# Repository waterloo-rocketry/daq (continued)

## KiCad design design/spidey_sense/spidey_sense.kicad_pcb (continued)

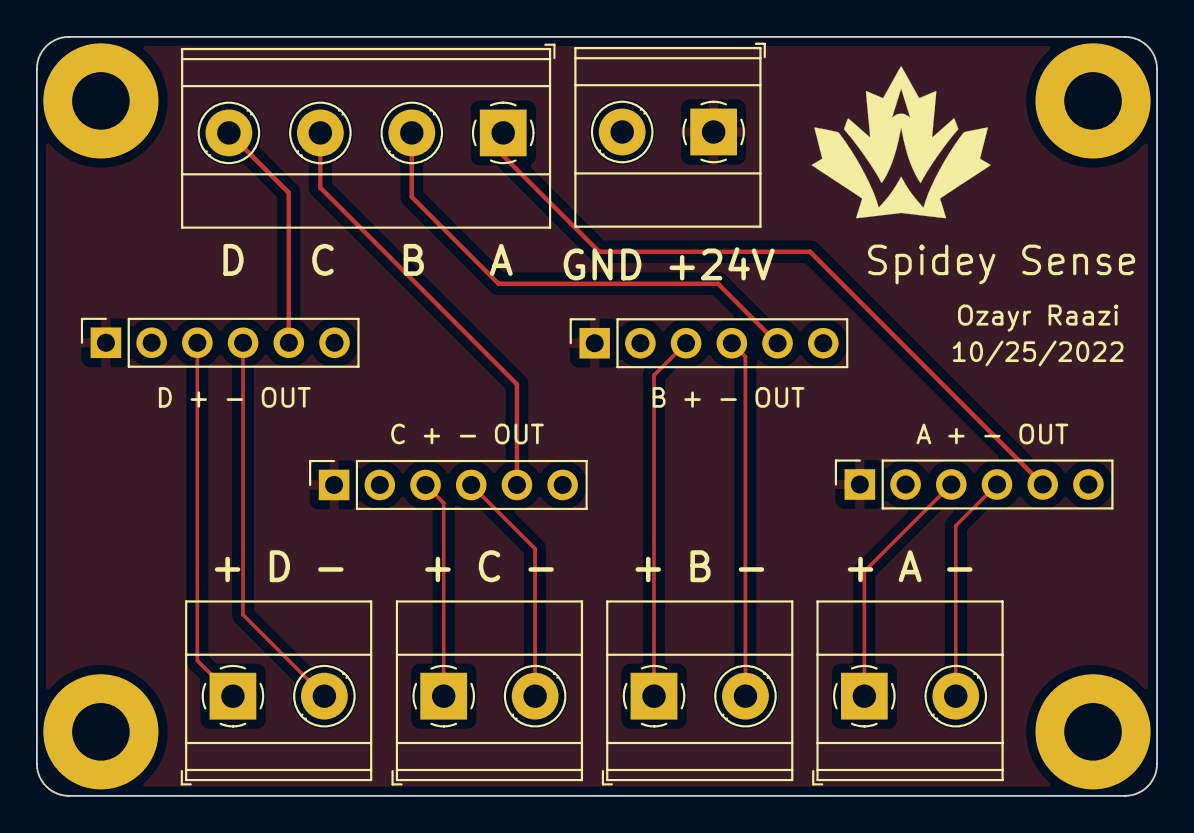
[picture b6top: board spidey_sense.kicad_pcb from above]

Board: 2 copper layers, 62.2 x 42.2 mm, 11 parts (0 on the bottom side), 14 nets.

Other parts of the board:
REF: MountingHole_3.2mm_M3_Pad

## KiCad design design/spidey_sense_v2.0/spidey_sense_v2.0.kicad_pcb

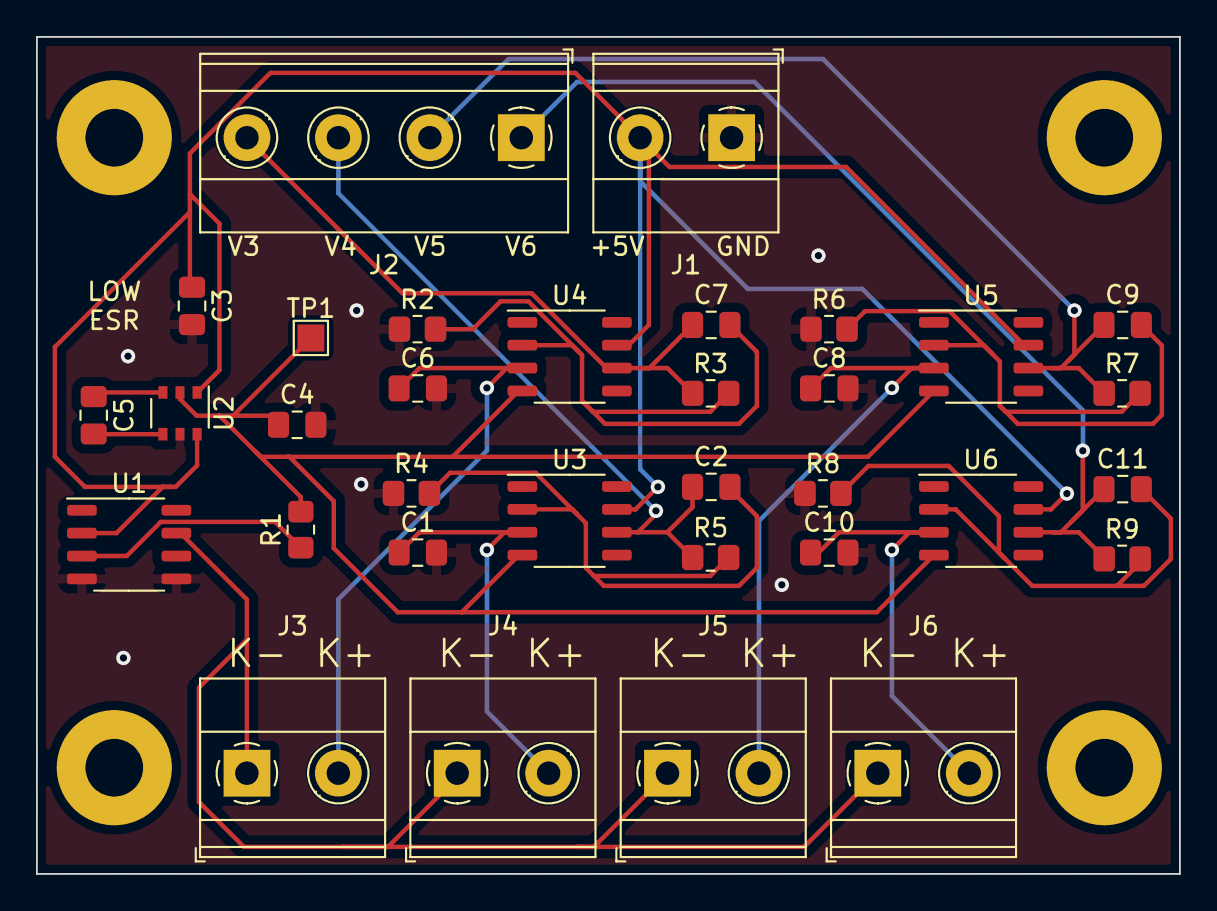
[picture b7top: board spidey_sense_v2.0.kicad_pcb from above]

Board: 2 copper layers, 63.5 x 46.5 mm, 33 parts (0 on the bottom side), 19 nets.

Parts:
C1, C2, C6, C7, C8, C9, C10, C11: 0.1uF; C_0805_2012Metric_Pad1.18x1.45mm_HandSolder
C3, C4: 10uF; C_0805_2012Metric_Pad1.18x1.45mm_HandSolder
C5: 1uF; C_0805_2012Metric_Pad1.18x1.45mm_HandSolder
J1: Input_Screw_Terminal; TerminalBlock_Phoenix_MKDS-1,5-2-5.08_1x02_P5.08mm_Horizont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
J2: Output_Screw_Terminal; TerminalBlock_Phoenix_MKDS-1,5-4-5.08_1x04_P5.08mm_Horizont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
J3, J4, J5, J6: Thermocouple_Terminal; TerminalBlock_Phoenix_MKDS-1,5-2-5.08_1x02_P5.08mm_Horizont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
R1: 150kΩ; R_0805_2012Metric_Pad1.20x1.40mm_HandSolder
R2, R4, R6, R8: 1kΩ; R_0805_2012Metric_Pad1.20x1.40mm_HandSolder
R3, R5, R7, R9: 17.3kΩ; R_0805_2012Metric_Pad1.20x1.40mm_HandSolder
TP1: TestPoint; TestPoint_Pad_1.5x1.5mm
U1: LT1025; SOP-8_3.9x4.9mm_P1.27mm
U2: LTC1983-5; TSOP-6_1.65x3.05mm_P0.95mm
U3, U4, U5, U6: LT1001; SOP-8_3.9x4.9mm_P1.27mm

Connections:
+5V: C3.1, J1.2, U1.2 (Vin), U2.1 (Vcc), U2.6 (SHDN), U3.7 (V+), U4.7 (V+), U5.7 (V+), U6.7 (V+)
-5V: C4.1, R1.2, TP1.1, U2.2 (Vout), U3.4 (V-), U4.4 (V-), U5.4 (V-), U6.4 (V-)
/Amplifier1/K+: C6.1, J3.2, U4.3 (+IN)
/Amplifier1/Vout: C7.1, J2.4, R3.1, U4.6 (OUT)
/Amplifier2/K+: C1.1, J4.2, U3.3 (+IN)
/Amplifier2/Vout: C2.1, J2.3, R5.1, U3.6 (OUT)
/Amplifier3/K+: C8.1, J5.2, U5.3 (+IN)
/Amplifier3/Vout: C9.1, J2.2, R7.1, U5.6 (OUT)
/Amplifier4/K+: C10.1, J6.2, U6.3 (+IN)
/Amplifier4/Vout: C11.1, J2.1, R9.1, U6.6 (OUT)
/K-: J3.1, J4.1, J5.1, J6.1, U1.7 (K/T)
GND: C1.2, C3.2, C4.2, C6.2, C8.2, C10.2, J1.1, R2.1, R4.1, R6.1, R8.1, U1.4 (GND), U1.5 (R-), U2.5 (GND)
unnamed: C2.2, R4.2, R5.2, U3.2 (-IN)
unnamed: C5.1, U2.3 (C+)
unnamed: C5.2, U2.4 (C-)
unnamed: C7.2, R2.2, R3.2, U4.2 (-IN)
unnamed: C9.2, R6.2, R7.2, U5.2 (-IN)
unnamed: C11.2, R8.2, R9.2, U6.2 (-IN)
unnamed: R1.1, U1.3 (V0)

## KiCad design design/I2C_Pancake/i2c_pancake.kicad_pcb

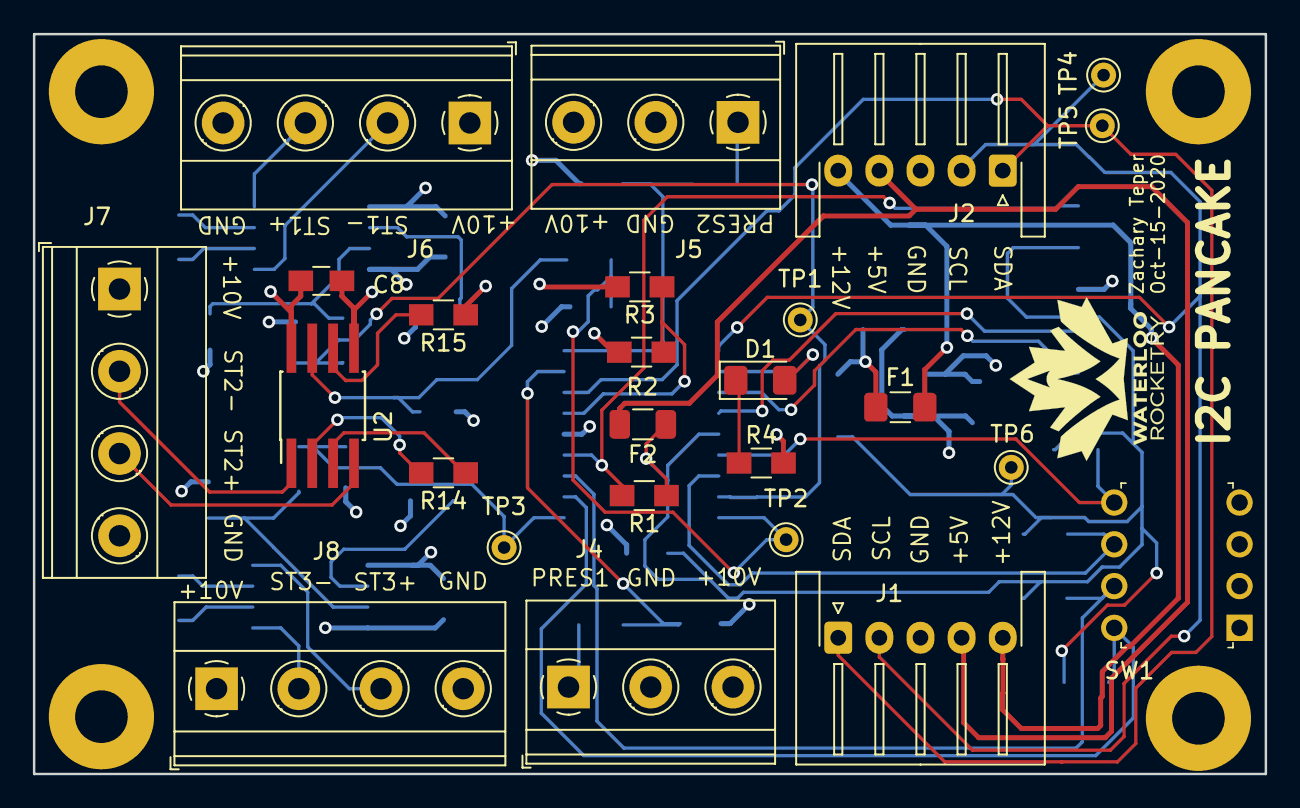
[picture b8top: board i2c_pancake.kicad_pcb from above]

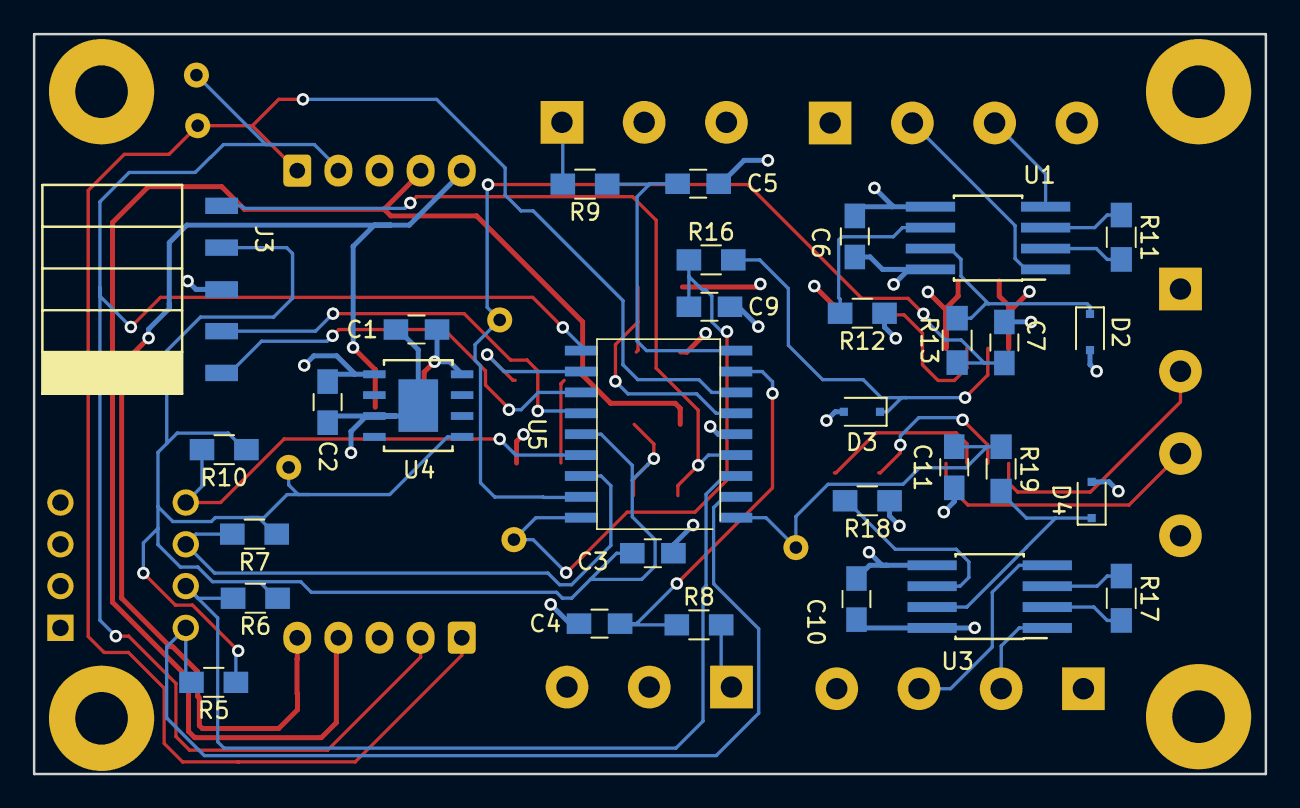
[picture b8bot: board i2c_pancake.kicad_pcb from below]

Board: 4 copper layers, 74.9 x 45.0 mm, 56 parts (31 on the bottom side), 43 nets.

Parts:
C1, C2, C4, C5, C7, C9, C11: 1 uF; C_0805_HandSoldering
C3, C6, C8, C10: 0.1uF; C_0805_HandSoldering
D1: LED; LED_1206_3216Metric_Pad1.42x1.75mm_HandSolder
D2, D3, D4: DDZ4V7ASF-7; D_SOD-323F
F1: Fuse; Fuse_1206_3216Metric_Pad1.42x1.75mm_HandSolder
F2: Fuse; Fuse_1206_3216Metric
J1, J2: Conn_01x05_Male; JST_XH_S5B-XH-A-1_1x05_P2.50mm_Horizontal
J3: Conn_01x05_Female; PinHeader_5x2.54_SMD_90deg_952-3198-1-ND
J4, J5: Conn_01x03; TerminalBlock_Phoenix_MKDS-1,5-3_1x03_P5.00mm_Horizontal
J6, J7, J8: Conn_01x04; TerminalBlock_Phoenix_MKDS-1,5-4_1x04_P5.00mm_Horizontal
R1, R2, R5, R6, R7, R10: 10K; R_0805_HandSoldering
R3: 5K; R_0805_HandSoldering
R4: 330; R_0805_HandSoldering
R8, R9, R13, R16, R19: 150; R_0805_HandSoldering
R11, R14, R17: R; R_0805_HandSoldering
R12, R15, R18: 0; R_0805_HandSoldering
SW1: SW_DIP_x04; DIP_SWITCH_4X2
TP1, TP2, TP3, TP4, TP5, TP6: TestPoint
U1, U2, U3: INA826; SOIC-8_3.9x4.9mm_Pitch1.27mm_HandSoldering
U4: BDJ0FC0WEFJ-E2
U5: PIC16F1826-ISO

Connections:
+5V: F2.2, J1.4, J2.4
+10V: C2.1, C6.2, C8.2, C10.2, J4.3, J5.3, J6.1, J7.1, J8.1, R2.1, U1.8, U2.8, U3.8, U4.1
+12V: F1.2, J1.5, J2.5
/DIP_1: R5.2, SW1.8, U5.2
/DIP_2: R6.2, SW1.7, U5.3
/DIP_3: R7.2, SW1.6, U5.16
/DIP_4: R10.2, SW1.5, U5.15
/ICSPCLK: J3.1, U5.12
/ICSPDAT: J3.2, U5.13
/P1_IN: J4.1, R8.2
/P2_IN: J5.1, R9.2
/PRESSURE_1: C4.1, R8.1, U5.8
/PRESSURE_2: C5.1, R9.1, U5.9
/SCL: J1.2, J2.2, TP4.1, U5.10
/SDA: J1.1, J2.1, TP5.1, U5.7
/STRAIN_OUT_1: C7.1, R13.1, TP1.1, U5.17
/STRAIN_OUT_2: C9.1, R16.1, TP2.1, U5.18
/STRAIN_OUT_3: C11.1, R19.1, TP3.1, U5.1
/~MCLR: J3.5, R1.2, U5.4
GND: C1.2, C2.2, C3.1, C4.2, C5.2, C6.1, C7.2, C8.1, C9.2, C10.1, C11.2, D2.2, D3.2, D4.2, J1.3, J2.3, J3.3, J4.2, J5.2, J6.4, J7.4, J8.4, R3.2, R4.2, R12.1, R15.1, R18.1, SW1.1, SW1.2, SW1.3, SW1.4, U1.5, U2.5, U3.5, U4.3, U4.EPAD, U5.5
unnamed: C1.1, F1.1, U4.8
unnamed: D1.1, R4.1
unnamed: D1.2, U5.11
unnamed: D2.1, R13.2, U1.7
unnamed: D3.1, R16.2, U2.7
unnamed: D4.1, R19.2, U3.7
unnamed: J6.2, U1.1
unnamed: J6.3, U1.4
unnamed: J7.2, U2.1
unnamed: J7.3, U2.4
unnamed: J8.2, U3.1
unnamed: J8.3, U3.4
unnamed: R2.2, R3.1, U5.6
unnamed: R11.1, U1.3
unnamed: R11.2, U1.2
unnamed: R12.2, U1.6
unnamed: R14.1, U2.3
unnamed: R14.2, U2.2
unnamed: R15.2, U2.6
unnamed: R17.1, U3.3
unnamed: R17.2, U3.2
unnamed: R18.2, U3.6
VDD: C3.2, F2.1, J3.4, R1.1, R5.1, R6.1, R7.1, R10.1, TP6.1, U4.5, U5.14

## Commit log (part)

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2017-12-23 Initial commit
    Add old schematics, datasheets, and strain gauge
    circuit preliminary design.
2017-12-25 Remove unused datasheets
2017-12-25 Add old labview and arduino code, NI manual
2017-12-27 Add git attributes
2018-01-02 Fix voltage monitoring, add gitignore
2018-01-04 Preliminary board layout (no tracks)
2018-01-04 Revised board layout
    - move screw terminal locations
    - power op amps from 10V line
    - misc connector numbering switches
2018-01-05 First pass board routing
    - will probably go back and change placement of power blocks
    - likely not final
2018-01-06 Board layout & routing rework
    - Move the power blocks further into the board
    - ground planing not done yet
2018-01-06 Make power traces fatter
2018-01-11 Correct PNP orientation in schematic
    Also swap out the part for one I have on hand (2N3906)
2018-01-12 Revise board connectors
2018-01-15 minor routing & silk screen changes
2018-02-27 Add thermistor schematic
2018-03-02 Fix INA126 reference biasing (sch)
2018-03-03 Reroute PCB and add schematic pdf.
2018-04-09 Add fuses to both strain gauge circuits.
2018-04-10 Finish routing on INA826 board.
2019-03-13 Add schematics and pcb files for thermistor board
2019-03-13 Update strain gauge design/fab files (non rtr)
2019-03-21 Add INA826 datasheet
2019-07-03 Add SOTS labview programs
    The labview program from the most recent static fire and an updated one with better formatting
2020-02-28 Labview Folder
    Made a new category to organize labview programs
2020-02-28 FYDP2020_Labview
    Updated version of Labview program that has adjustable data logging and graph update periods, better formatted code, live display of data production/consumption delay, and reformatted graphs.
2020-02-28 Static Fire Changes
    Reordered sensors in DAQ assistant for SF setup and new sensors, added another graph for 5th pressure sensor, changed order of data logged in file, removed filtering on arbitrary readings.
2020-02-28 Minor Changes
    Program tested, data is logged properly from the right sensors.
2020-02-28 Update calibration values
2020-03-03 Same as last commit
    Version used for March 1 SF
2020-03-10 Create initial schematic for i2c pancake board
2020-03-12 Add MCU and finish schematic
2020-03-21 Fix some suggestions
2020-04-29 Replace internal DC power supply with a Low-Dropout Regulator
    The LDO regulator will convert the 12 volt input from the LiPo battery to a stable 10 volt
    internal supply.
2020-05-10 Update component footprints to prepare for PCB Layout update
    The footprints of many components in the I2C Pancake Board
    design have been updated to prepare for a new PCB Layout.
2020-06-01 Finish the preliminary PCB layout
    The preliminary PCB layout is finished. However, there is
    room for improvement. The PCB layout should be reviewed and
    polished before continuing with routing.
2020-06-14 Improve Layout of Passive Components on the Pancake Board
    -Fuse has been replaced with a 1206 polyfuse
    -passive components have been rearranged in a more logical manner
    -DRC rules have been imported from the RLCS v2 project
2020-07-05 Add pinout labels to connectors
2020-07-05 Finished first version of routing
2020-07-05 Fix some bad routing and silkscreen placement
2020-07-09 Add unneeded KiCad files to .gitignore
    All KiCad file exclusions from the official KiCad .gitignore template, except for the BOM files, have been added.
    While .bak and .bck temporary files were being ignored, there are many more KiCad file types that should not be on the VCS. These include auto-saves, cache files, backup files, netlist files (they sh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
2020-07-09 Remove all files in .gitignore
2020-07-12 Remove unecessary KiCAD files.
    The .gitignore has been updated to ignore KiCAD backup and cache files.
2020-07-13 Revert "Add pinout labels to connectors"
    This reverts commit 21ee90c71cbcb3ee9da454b06d43e90a118cf2fc.
2020-07-20 Modify the board settings to have four layers.
    Pinout labels have been moved to the top of the board.
2020-07-20 Updated design rules
2020-07-20 Improve board routing.
    Coupling/decoupling capacitors are now closely connected to their
    respective devices.
2020-08-23 Increase I2C line clearance to 20 mils.
    This will minimize cross-talk with I2C lines.
2020-08-23 Add test points to the Pancake board.
    Test points were added to the outputs of each strain guage amp.
2020-08-23 Improve SCL track spacing.
2020-09-23 Replace +5V and +12V routing with 12 traces
2020-09-23 Finish I2C Pancake board design and add gerbers!
2020-09-23 Update PCB
2020-09-30 Add pdf version of PCB design
2020-10-03 Add schematic PDF
2020-10-03 Add gerbers
2020-10-10 Add RC filters to the analog inputs of the PIC
    This commit also includes a new and improved routing.
2020-10-11 Repair broken and missing library references
2020-10-11 Rename "I2C Pancake" to "I2C_Pancake" and update gerbers
2020-10-15 Fix routing for +5V trace
2020-10-15 Repair broken library references
2020-10-15 Add excelon drill files.
2020-11-30 Include necessary files for setting up in-flight recording, with instructions
2020-12-06 Modify bash script to flush video output buffer to file.
2021-04-06 Add SSH details to readme
2021-05-22 Create initial commit for SPI temp sensing board
2021-05-25 Finish schematic desing
2021-05-26 Add initial part layout.
2021-05-27 Add silkscreen and gerbers
2021-06-05 Add simultaneous stream and save of footage
2021-06-05 Add dynamic video title
2021-06-05 Address PR comments
2021-06-05 Add more detail to readme
2021-06-05 Add details about fixing line endings for the .sh, .service files
2021-06-06 Change stream to FFMPEG and MPV
2021-06-07 Fix GPU_MEM number
2021-06-07 Inflight recording (#11)
    * Include necessary files for setting up in-flight recording, with instructions
2021-06-25 Update picam documentation
2021-06-25 Fix mistake
2021-06-25 Remove unneeded 'a'
2021-06-25 Fix picam documentation (#12)
    * Update picam documentation
2021-08-13 Add PDF of schematic
2021-08-22 Address review comments
2021-09-23 Address comments from Lance
2021-10-04 Changed some capacitors based on the LDO's application note / suggested layout, layout done
2021-10-16 Layout tweaks, first pass at routing
2021-10-19 Fix inconsistent silkscreen positions
2021-10-20 Oh yes the silkscreen is a thing that exists
2021-11-22 Initial schematic
2021-11-24 Generate gerbers
2021-12-03 Updated Spidey Sense v2 board
2021-12-04 Second design for Spidey Sense
2021-12-12 Updated designs
2021-12-12 Adjusted name position
2021-12-21 Tweak value of C3, replace U1 with the part we ordered
2021-12-21 Update pdf, pcb
2021-12-22 Tweaking labels and added test point
2022-01-16 Designed PCB
2022-01-19 Updated PCB
2022-01-21 Removed traces and daisy-chaining
2022-01-23 Organized spidey_sense
2022-01-26 gitignore for KiCAD 6
2022-01-27 Update gitignore
2022-01-27 Added vias to avoid GND loops
2022-01-30 Changed C5 value
2022-04-05 Change from "autovid" to "picam", update scripts to be easier to setup (#17)
    * Change from "autovid" to "picam", update scripts to be easier to setup
2022-05-18 Allow PiCam to communicate with the PiCam HAT using UART
    **The changes in this commit have not been tested!
2022-05-22 Add a new "uart" service to manage UART communication
2022-05-23 Add UART service to the setup script
2022-06-15 fixes for comp
2022-10-11 Initial schematic design
2022-10-12 Changed component orientations and added labels
2022-10-12 Routed all traces and set manufacturing constraints
2022-10-24 Changed pin header orientations and added silkscreen labels
2023-10-27 First Schematic Editing
    Basic Sensor layout for 1 sensor
2023-10-28 Changes to delete switches and duplicate board setup
2023-11-04 Connection for 2 thermistors or 4-20 amp sensors
    Added option for 4th connector to also be power port and doubled resistors to allow for two thermistors or 4-20 amp sensors
2023-11-12 Added Netlabels and Fuse
    Cleaned up the schematic and added a 50mA fuse to the power lines
    Still need to rename jumpers and add RC low pass filter to data lines
2023-11-12 Create power_board2
2023-11-13 Jack Edits and Aesthetic Stuff
    Made sure the nets for the RC filter input are not connected to the output.
    Renamed the jumpers to something meaningful
2023-11-19 Create keep
2023-11-20 Added Footprints for Most Components
    Footprints for all components except for 4 way jumper added
    Jason comments on PR also added
2023-12-04 Updated Footprint for 4 way jumper to 1 mm through hole
2023-12-09 Something
2023-12-09 Repo Cleaning
2023-12-10 First Half of Changes
2023-12-10 More Requested Changes
2023-12-16 Changed footprint Changed footprint path changed footprint Edit Edit Edit
2023-12-16 12 Pole Board Connector
    Schematic Symbol and footprint for the 12 pole board connector created
2023-12-17 Footprint and Hierarchal Sheets
    Footprint for 6 screw terminal block added and sensor components made into hierarchical sheets
2023-12-18 Edited calculations
2023-12-23 Files Renamed and Changes Implemented
    Renamed project to Daq Patch Panel
    Updated 4 way jumper footprints
    Renamed input screw terminal
2024-01-01 Latest Review Changes
2024-01-12 Renamed file
2024-01-12 Added file
2024-01-12 Changed layout of ldo
2024-01-14 Added LED
2024-01-18 Minor Grouping of Components for Routing
2024-01-23 More Layout Edits
2024-01-23 More Layout Changes
2024-01-24 Possible Internal Routing, no pours for gnd and power done yet
2024-01-26 Fixes of Screw Terminal Direction
    Rotated screw terminals cause they were backwards :skull:
2024-01-28 Revert "Fixes of Screw Terminal Direction"
    This reverts commit f2852c9006a7d32005e30de1d4edca6d561d1619.
2024-01-29 Updated LED calculations, diodes, LDO symbol
2024-01-29 Updated buck diode
2024-01-29 shifted ldo schematic
2024-02-01 ReLayout and Routing in Progress
2024-02-08 Second Try at Routing (Cleanup Needed)
    Alternate Routing of Traces, needs to input pours and simplification
2024-02-08 2 Vias Removed
2024-02-08 Routing Changes, Pours Added
    Needs to be tidied up before review
2024-02-08 Tried to Pour
    Tryed to pour,
2024-02-10 board layout
2024-02-11 edited layout
2024-02-15 Moved capacitors up
2024-02-16 changed name of board
2024-03-02 Removed old spidey sense files and added new thermocouple board schematic
2024-03-02 Deleted remaining spidey sense files
2024-03-04 Added logo and aligned J2 and J1
2024-03-05 Added optional can termination resistor
2024-03-05 Changes Made, Length Reduced
2024-03-05 Ready for Review
2024-03-08 Actually Ready for Review This Time
2024-03-10 Added Logo, Name, and Board Name
2024-03-10 routing
2024-03-11 Miles/Ash Changes Implemented
2024-03-11 Fixed Traces Running Through Din Screw Holes
2024-03-12 Addressed comments added 3.3V PIC
2024-03-12 Fixed Jason's Comments
2024-03-12 Moved Logo
2024-03-12 quick layout thrown together
2024-03-14 Finished board routing
2024-03-14 swag
2024-03-14 Comments Addressed and wire bit removed
2024-03-15 Addressed comments
2024-03-15 Rotated Rocketry Logo to be in line with name direction
2024-03-15 Daq power board (#22)
    * Create power_board2
    * Add files via upload
    * Add files via upload
    * Delete design/power_board2
    * Create keep
    * Update and rename design/buck_converter_new.kicad_sch to design/power_board_2/buck_converter_new.kicad_sch
2024-03-15 Thermocouple board (#23)
    * Removed old spidey sense files and added new thermocouple board schematic
    * Deleted remaining spidey sense files
    * Renamed SDI tag to SDO
    * Added optional can termination resistor
    * Addressed Artem's comments
    * Addressed comments added 3.3V PIC
2024-07-28 Added the Schematic as a PDF to the sheet and adde d some comments to the internal sheet
2024-07-28 more cosmetic changes
2025-07-05 Move old things into old/
2025-07-06 80% of schematic done
2025-07-09 Layout v1, its bad
2025-07-09 More footprints
2025-07-10 Layout v2; better
2025-07-23 First draft PCB
2025-07-25 Layout for prod, v1
